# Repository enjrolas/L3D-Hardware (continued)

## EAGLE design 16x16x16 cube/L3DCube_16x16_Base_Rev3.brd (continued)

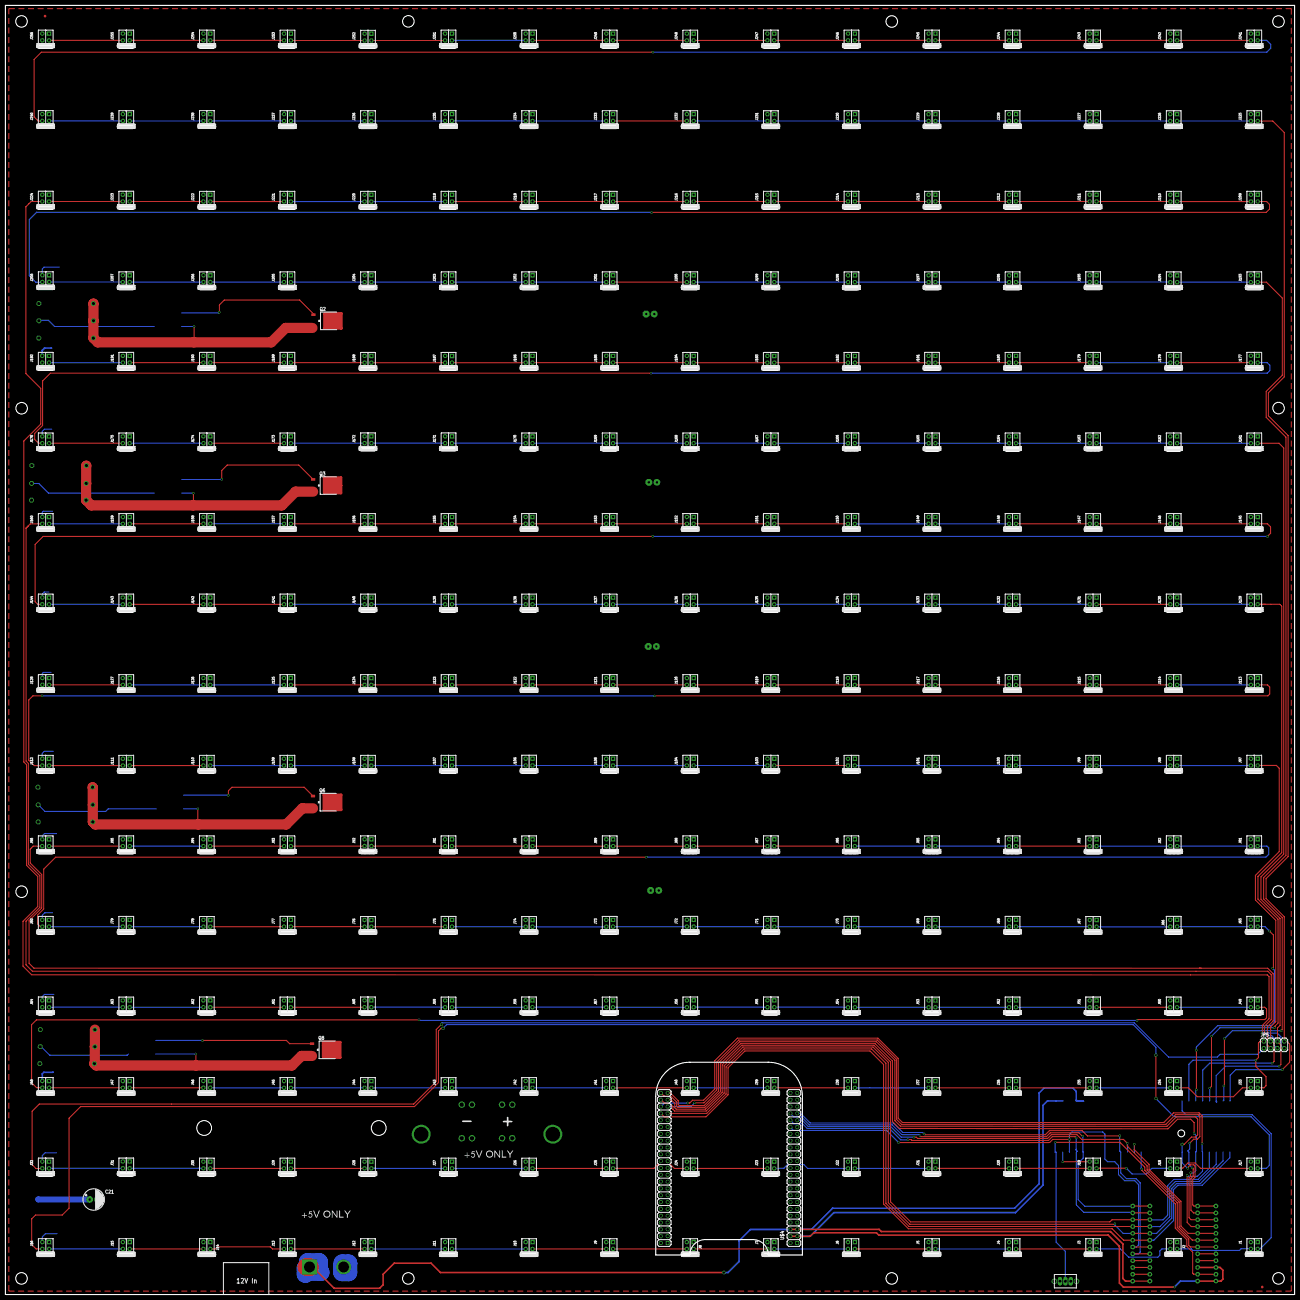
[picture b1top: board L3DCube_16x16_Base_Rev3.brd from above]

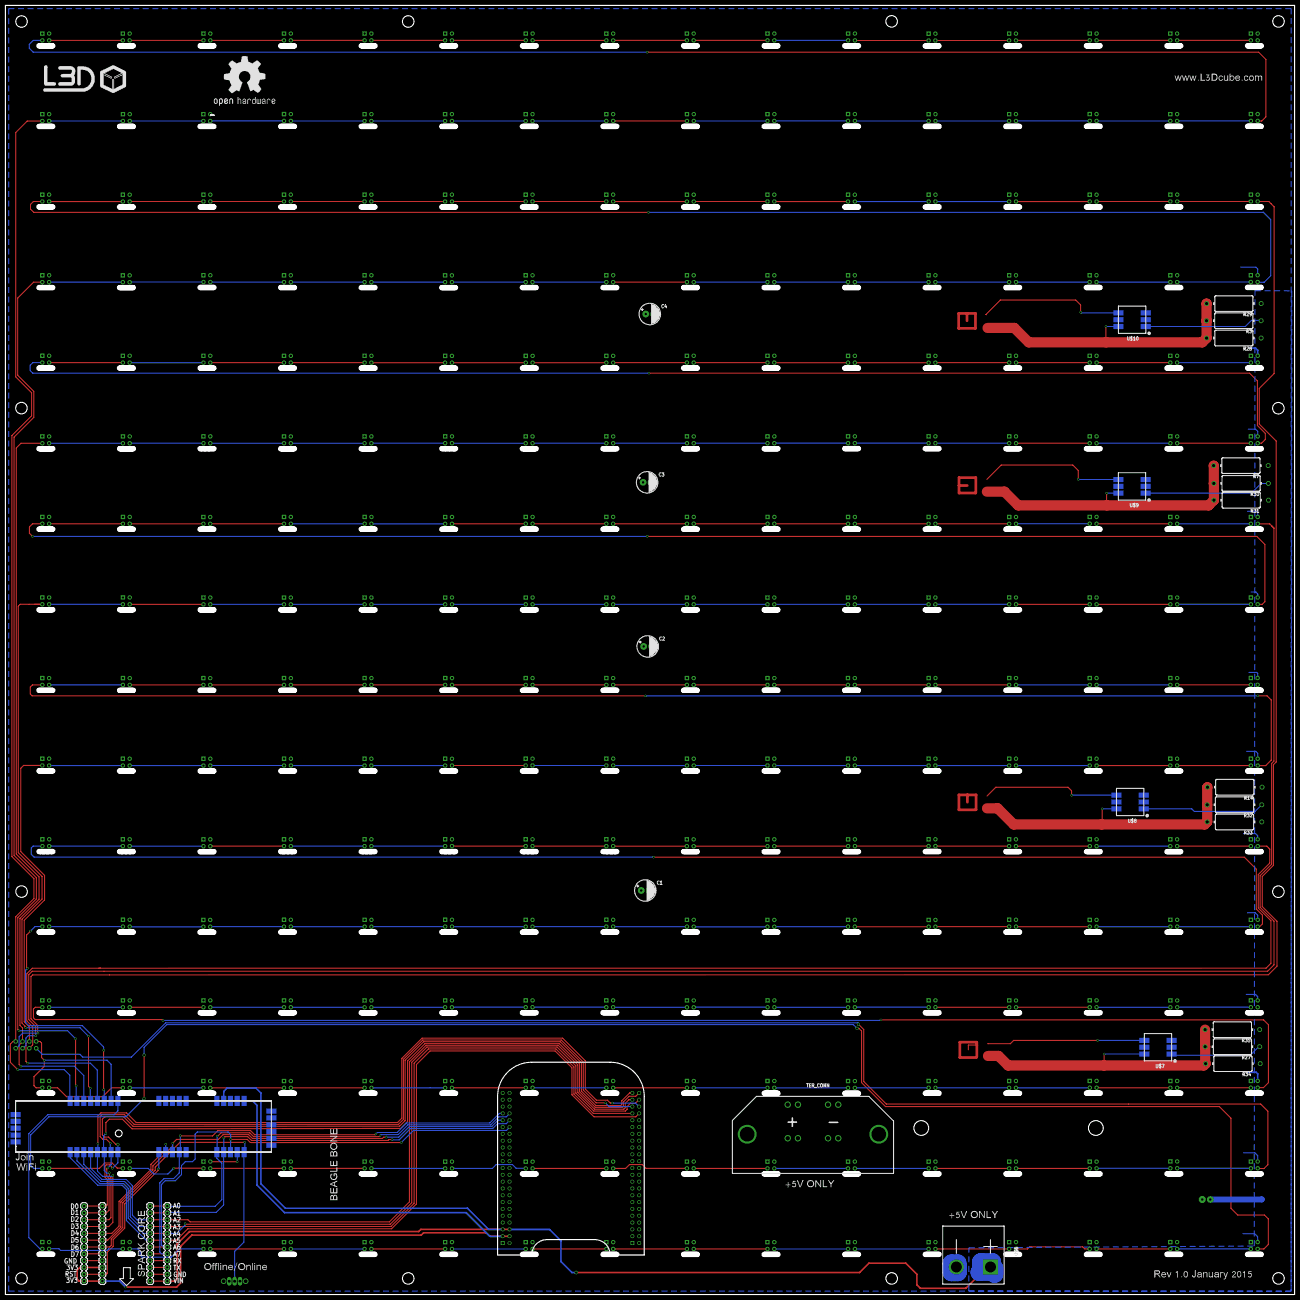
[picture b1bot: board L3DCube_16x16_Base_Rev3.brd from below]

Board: 2 copper layers, 480.0 x 480.0 mm, 295 parts (25 on the bottom side), 291 nets.

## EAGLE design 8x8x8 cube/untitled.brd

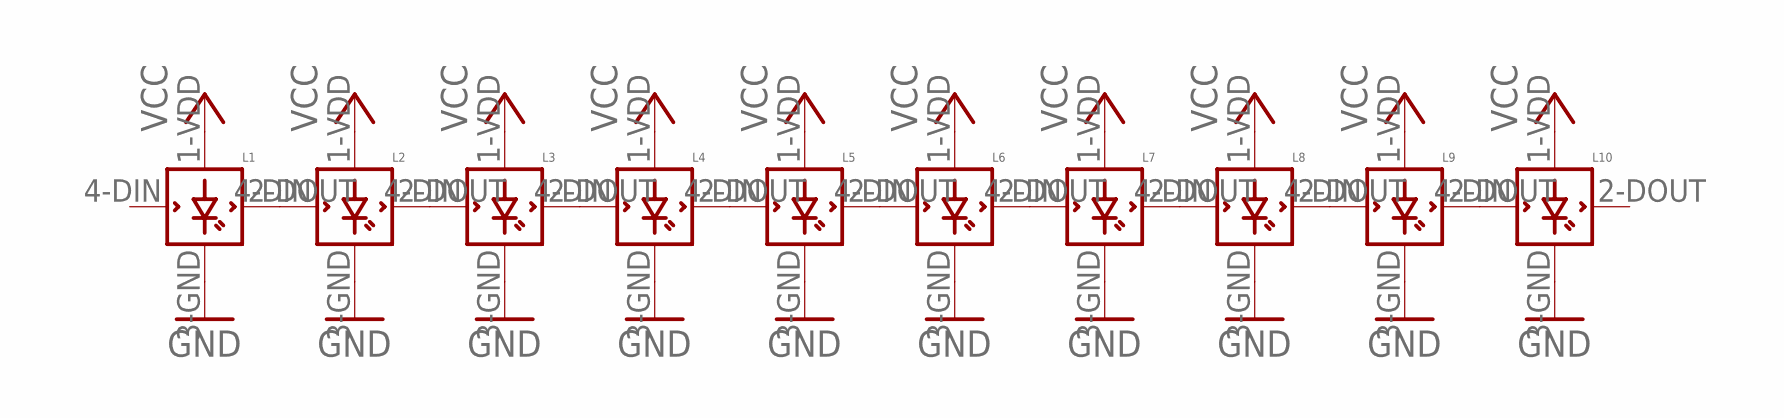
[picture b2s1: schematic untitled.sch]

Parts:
L1, L2, L3, L4, L5, L6, L7, L8, L9, L10: WS2812B

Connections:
GND: L1.3-GND (GND), L2.3-GND (GND), L3.3-GND (GND), L4.3-GND (GND), L5.3-GND (GND), L6.3-GND (GND), L7.3-GND (GND), L8.3-GND (GND), L9.3-GND (GND), L10.3-GND (GND)
unnamed: L1.2-DOUT (DOUT), L2.4-DIN (DIN)
unnamed: L3.2-DOUT (DOUT), L4.4-DIN (DIN)
unnamed: L5.2-DOUT (DOUT), L6.4-DIN (DIN)
unnamed: L7.2-DOUT (DOUT), L8.4-DIN (DIN)
unnamed: L8.2-DOUT (DOUT), L9.4-DIN (DIN)
unnamed: L9.2-DOUT (DOUT), L10.4-DIN (DIN)
VCC: L1.1-VDD (VDD), L2.1-VDD (VDD), L3.1-VDD (VDD), L4.1-VDD (VDD), L5.1-VDD (VDD), L6.1-VDD (VDD), L7.1-VDD (VDD), L8.1-VDD (VDD), L9.1-VDD (VDD), L10.1-VDD (VDD)

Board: 2 copper layers, 10 parts (0 on the bottom side), 8 nets, no tracks yet.

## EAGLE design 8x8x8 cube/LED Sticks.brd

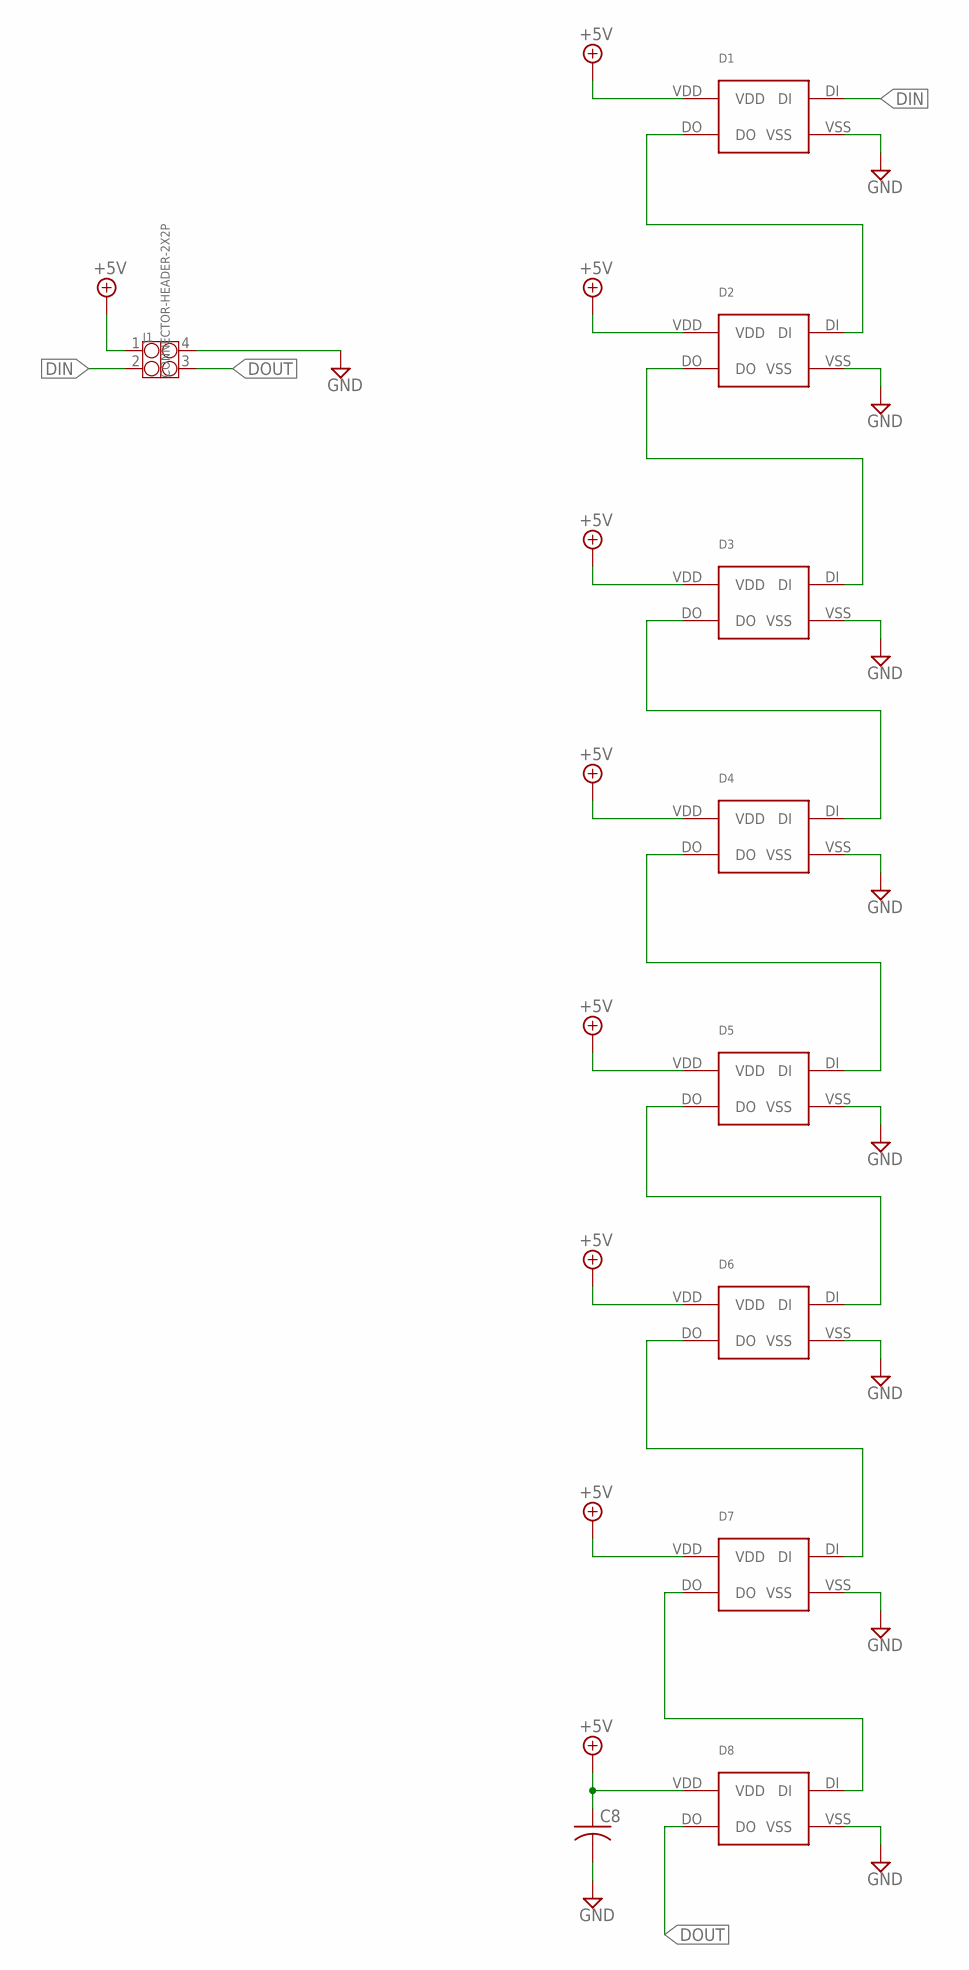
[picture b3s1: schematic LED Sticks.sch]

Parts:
C8: C-USC0603K; C0603K
D1, D2, D3, D4, D5, D6, D7, D8: WS2812B
J1: CONNECTOR-HEADER-2X2P; 2X2P-2.54

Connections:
+5V: C8.1, D1.VDD, D2.VDD, D3.VDD, D4.VDD, D5.VDD, D6.VDD, D7.VDD, D8.VDD, J1.1
DIN: D1.DI, J1.2
DOUT: D8.DO, J1.3
GND: C8.2, D1.VSS, D2.VSS, D3.VSS, D4.VSS, D5.VSS, D6.VSS, D7.VSS, D8.VSS, J1.4
unnamed: D1.DO, D2.DI
unnamed: D2.DO, D3.DI
unnamed: D3.DO, D4.DI
unnamed: D4.DO, D5.DI
unnamed: D5.DO, D6.DI
unnamed: D6.DO, D7.DI
unnamed: D7.DO, D8.DI

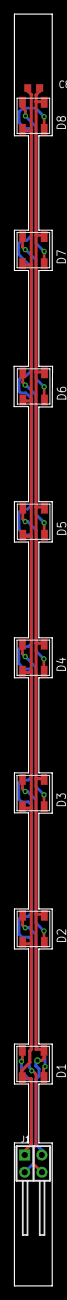
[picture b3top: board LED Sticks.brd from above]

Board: 2 copper layers, 5.7 x 187.5 mm, 10 parts (0 on the bottom side), 11 nets.

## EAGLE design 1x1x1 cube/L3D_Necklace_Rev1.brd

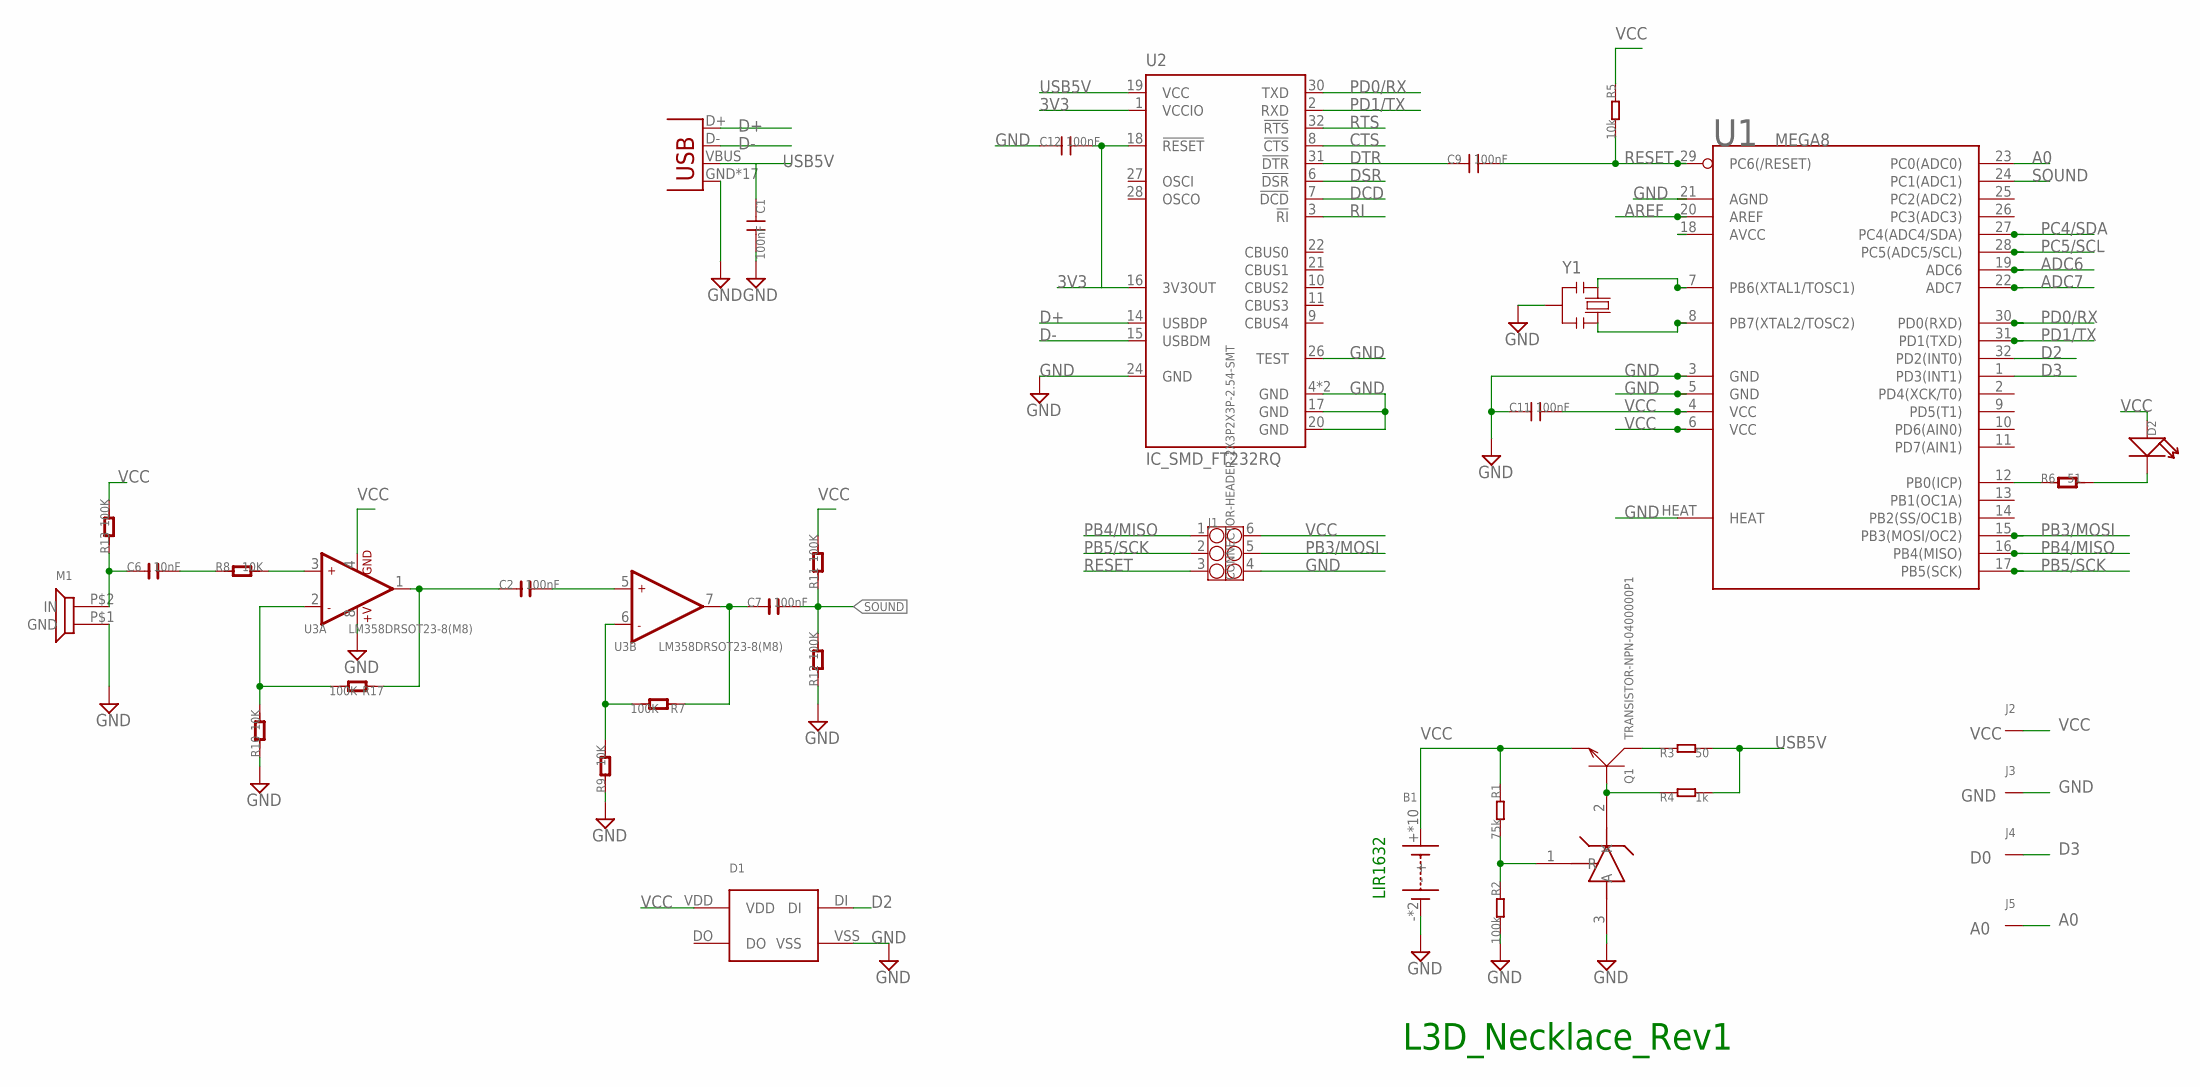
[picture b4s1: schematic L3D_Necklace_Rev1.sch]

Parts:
B1: BUTTONCELLLIR1632; BUTTONCELL_LIR1632
C1, C9, C11, C12: 100nF; 0603
C2, C7: 100nF; C0603
C6: 10nF; C0603
D1: WS2812BWS2812B_STANDARD; WS2812B_STANDARD
D2: LEDLED1206; LED1206
J1: CONNECTOR-HEADER-2X3P2X3P-2.54-SMT; 2X3P-2.54-SMT
J2: VCC; 1R5MM-HOLE
J3: GND; 1R5MM-HOLE
J4: D0; 1R5MM-HOLE
J5: A0; 1R5MM-HOLE
JP1: USBUSB-MICROB-SLOT-HOLE; USB-MICROB-SLOT-HOLE
M1: MICROPHONEMICROPHONE_1*3MM; MICROPHONE_1*3MM
Q1: TRANSISTOR-NPN-0400000P1; SOT23
R1: 75k; 0603
R2: 100k; 0603
R3: 50; 0603
R4: 1k; 0603
R5: 10k; 0603
R6: 51; R0603
R7, R11, R12, R13, R17: 100K; R0603
R8, R9, R10: 10K; R0603
U1: MEGA8; MLF32X
U2: IC_SMD_FT232RQ; IC_SMD_QFN32
U3: LM358DRSOT23-8(M8); SOT-23-8(M8)
Y1: SMARTPRJ_RESONATORMU; SMARTPRJ_RESONATOR
Z1: TL431; SOT23

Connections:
3V3: C12.2, U2.1 (VCCIO), U2.16 (3V3OUT), U2.18 (!RESET)
A0: J5.P$1, U1.23 (PC0(ADC0))
ADC6: U1.19 (ADC6)
ADC7: U1.22 (ADC7)
AREF: U1.20 (AREF)
CTS: U2.8 (!CTS)
D2: D1.DI, U1.32 (PD2(INT0))
D3: J4.P$1, U1.1 (PD3(INT1))
D+: JP1.D+, U2.14 (USBDP)
D-: JP1.D-, U2.15 (USBDM)
DCD: U2.7 (!DCD)
DSR: U2.6 (!DSR)
DTR: C9.1, U2.31 (!DTR)
GND: B1.-, B1.-' (-), C1.2, C11.1, C12.1, D1.VSS, J1.4, J3.P$1, JP1.GND, JP1.MT1 (GND), JP1.MT2 (GND), JP1.MT3 (GND), JP1.MT4 (GND), JP1.MT5 (GND), JP1.MT6 (GND), JP1.MT7 (GND), JP1.MT8 (GND), JP1.MT9 (GND), JP1.MT10 (GND), JP1.MT11 (GND), JP1.MT12 (GND), JP1.P$1 (GND), JP1.P$2 (GND), JP1.P$3 (GND), JP1.P$4 (GND), M1.P$1 (GND), R2.2, R9.1, R10.1, R12.1, U1.3 (GND), U1.5 (GND), U1.21 (AGND), U1.HEAT, U2.4 (GND), U2.17 (GND), U2.20 (GND), U2.24 (GND), U2.26 (TEST), U2.EXP (GND), U3.8 (+V), Y1.2, Z1.3 (A)
unnamed: R1.2, R2.1, Z1.1 (R)
unnamed: Q1.1 (B), R4.1, Z1.2 (K)
unnamed: R8.2, U3.3 (+IN1)
unnamed: Q1.3 (C), R3.1
unnamed: C2.1, R17.1, U3.1 (OUT1)
unnamed: R6.1, U1.12 (PB0(ICP))
unnamed: D2.-, R6.2
unnamed: R10.2, R17.2, U3.2 (-IN1)
unnamed: C7.1, R7.1, U3.7 (OUT2)
unnamed: C2.2, U3.5 (+IN2)
unnamed: R7.2, R9.2, U3.6 (-IN2)
unnamed: C6.2, R8.1
unnamed: C6.1, M1.P$2 (IN), R13.1
PB3/MOSI: J1.5, U1.15 (PB3(MOSI/OC2))
PB4/MISO: J1.1, U1.16 (PB4(MISO))
PB5/SCK: J1.2, U1.17 (PB5(SCK))
PC4/SDA: U1.27 (PC4(ADC4/SDA))
PC5/SCL: U1.28 (PC5(ADC5/SCL))
PD0/RX: U1.30 (PD0(RXD)), U2.30 (TXD)
PD1/TX: U1.31 (PD1(TXD)), U2.2 (RXD)
RESET: C9.2, J1.3, R5.2, U1.29 (PC6(/RESET))
RI: U2.3 (!RI)
RTS: U2.32 (!RTS)
SOUND: C7.2, R11.1, R12.2, U1.24 (PC1(ADC1))
USB5V: C1.1, JP1.VBUS, R3.2, R4.2, U2.19 (VCC)
VCC: B1.+, B1.+1' (+), B1.P$3 (+), B1.P$4 (+), B1.P$5 (+), B1.P$6 (+), B1.P$7 (+), B1.P$8 (+), B1.P$9 (+), B1.P$10 (+), C11.2, D1.VDD, D2.+, J1.6, J2.P$1, Q1.2 (E), R1.1, R5.1, R11.2, R13.2, U1.4 (VCC), U1.6 (VCC), U1.18 (AVCC), U3.4 (GND)
XTAL1: U1.7 (PB6(XTAL1/TOSC1)), Y1.1
XTAL2: U1.8 (PB7(XTAL2/TOSC2)), Y1.3

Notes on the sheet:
L3D_Necklace_Rev1
LIR1632

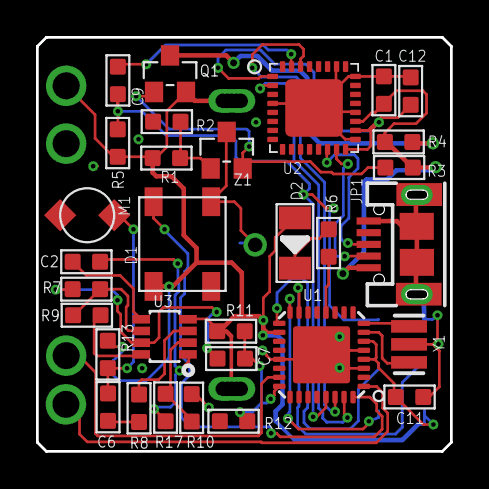
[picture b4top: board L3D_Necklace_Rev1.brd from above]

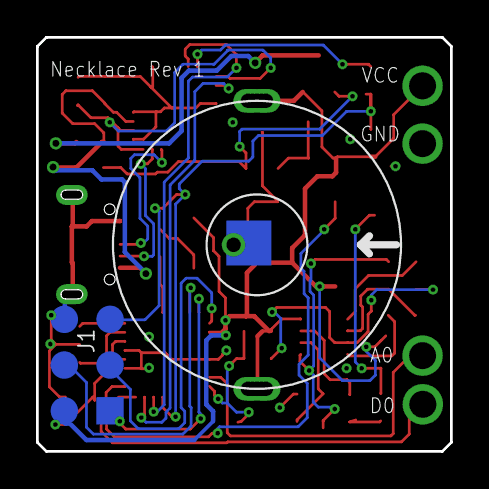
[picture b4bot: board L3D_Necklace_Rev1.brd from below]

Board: 2 copper layers, 23.0 x 23.0 mm, 37 parts (2 on the bottom side), 32 nets.

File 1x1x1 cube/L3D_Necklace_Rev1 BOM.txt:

Partlist exported from /Users/japhy/Downloads/L3D-Hardware-master/1x1x1 cube/L3D_Necklace_Rev1.sch at 4/11/16 1:42 PM

Part Value                              Device                             Package              Description                                                             
B1   BUTTONCELLLIR1632                  BUTTONCELLLIR1632                  BUTTONCELL_LIR1632                                                                           
C1   100nF                              C-0603                             0603                 Ceramic Capacitors                                                      
C2   100nF                              C-0603                             C0603                                                                                        
C6   10nF                               C-0603                             C0603                                                                                        
C7   100nF                              C-0603                             C0603                                                                                        
C9   100nF                              C-0603                             0603                 Ceramic Capacitors                                                      
C11  100nF                              C-0603                             0603                 Ceramic Capacitors                                                      
C12  100nF                              C-0603                             0603                 Ceramic Capacitors                                                      
D1                                      WS2812BWS2812B_STANDARD            WS2812B_STANDARD                                                                             
D2                                      LEDLED1206                         LED1206              LED                                                                     
J1   CONNECTOR-HEADER-2X3P2X3P-2.54-SMT CONNECTOR-HEADER-2X3P2X3P-2.54-SMT 2X3P-2.54-SMT                                                                                
J2   VCC                                1R5MM-HOLE                         1R5MM-HOLE                                                                                   
J3   GND                                1R5MM-HOLE                         1R5MM-HOLE                                                                                   
J4   D0                                 1R5MM-HOLE                         1R5MM-HOLE                                                                                   
J5   A0                                 1R5MM-HOLE                         1R5MM-HOLE                                                                                   
JP1  USBUSB-MICROB-SLOT-HOLE            USBUSB-MICROB-SLOT-HOLE            USB-MICROB-SLOT-HOLE                                                                         
M1   MICROPHONEMICROPHONE_1*3MM         MICROPHONEMICROPHONE_1*3MM         MICROPHONE_1*3MM                                                                             
Q1   TRANSISTOR-NPN-0400000P1           TRANSISTOR-NPN-0400000P1           SOT23                S9013：NPN Transistor                                                    
R1   75k                                R-0603                             0603                                                                                         
R2   100k                               R-0603                             0603                                                                                         
R3   50                                 R-0603                             0603                                                                                         
R4   1k                                 R-0603                             0603                                                                                         
R5   10k                                R-0603                             0603                                                                                         
R6   51                                 R-0603                             R0603                                                                                        
R7   100K                               R-0603                             R0603                                                                                        
R8   10K                                R-0603                             R0603                                                                                        
R9   10K                                R-0603                             R0603                                                                                        
R10  10K                                R-0603                             R0603                                                                                        
R11  100K                               R-0603                             R0603                                                                                        
R12  100K                               R-0603                             R0603                                                                                        
R13  100K                               R-0603                             R0603                                                                                        
R17  100K                               R-0603                             R0603                                                                                        
U1   MEGA8                              MEGA8                              MLF32X                                                                                       
U2   IC_SMD_FT232RQ                     IC_SMD_FT232RQ                     IC_SMD_QFN32         Source: http://www.ftdichip.com/Documents/DataSheets/DS_FT232R_v104.pdf 
U3   LM358DRSOT23-8(M8)                 LM358DRSOT23-8(M8)                 SOT-23-8(M8)         General purpose LOW Voltage, Rail-to-Rail Output Amplifiers             
Y1   SMARTPRJ_RESONATORMU               SMARTPRJ_RESONATORMU               SMARTPRJ_RESONATOR                                                                           
Z1   TL431                              TL431SOT23                         SOT23

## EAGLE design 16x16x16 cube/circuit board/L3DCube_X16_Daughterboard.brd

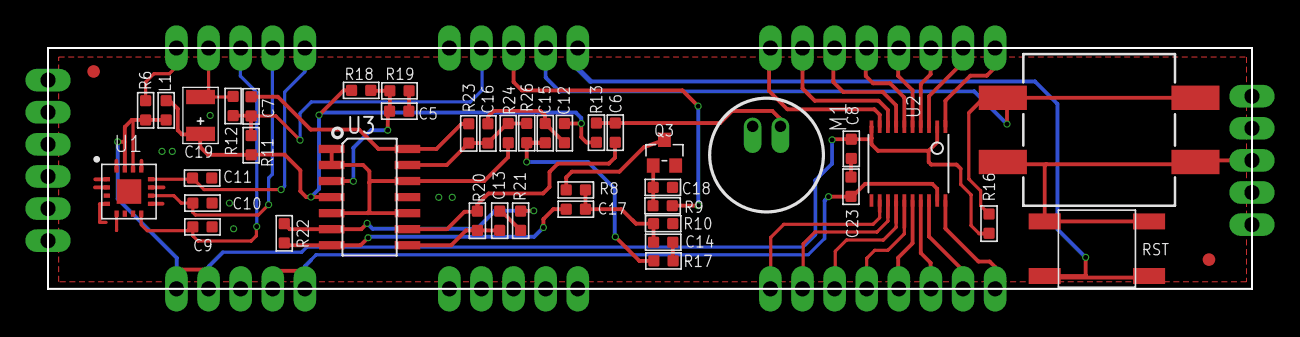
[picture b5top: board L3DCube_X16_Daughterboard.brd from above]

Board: 2 copper layers, 95.2 x 19.1 mm, 44 parts (0 on the bottom side), 43 nets.

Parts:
C5: 10uF; C0603
C6, C7, C8, C9, C10, C11, C12, C13, C18, C23: 100nF; C0603
C14, C17: 220nF; C0603
C15: 10nF; C0603
C16: 680pF; C0603
C19: 220uF; AVX-B
K2: BUTTON-4P; 4P-12X12X6-SMD
L1: 2.2uH; L0603
M1: MICROPHONE
Q3: 2N7002; SOT23
R6, R9, R10, R16, R20, R21, R26: 10K; R0603
R8: 33; R0603
R11, R12, R18, R19: 100K; R0603
R13: 4.3K; R0603
R17: 1K; R0603
R22: 220K; R0603
R23: 180K; R0603
R24: 3.3M; R0603
RST: BUTTON-4P-3100010P1; 4P-SMD-6.0X6.0X5.0H
U1: ADXL335
U2: TSSOP20
U3: LMV324IDR-1100030P1; SOIC14
U$1: CUBE-16-DAUGHTERBOARD
U$2, U$3: FIDUCIAL-MARK

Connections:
!RST: RST.2, RST.3, U$1.RST
+3V3: C8.2, L1.2, R6.1, R16.1, U1.VSS1, U1.VSS2, U2.2, U2.10, U$1.3V3, U$1.3V3'
+5V: C23.2, U2.19, U$1.5V, U$1.5V'
A2: U2.6, U$1.IN3
A3: U2.7, U$1.IN2
A4: U2.8, U$1.IN1
A5: U2.9, U$1.IN0
D0: U2.1, U$1.IN7
D1: U2.3, U$1.IN6
D2: U2.4, U$1.IN5
D3: U2.5, U$1.IN4
DIN_1: U2.20, U$1.OUT7
DIN_2: U2.18, U$1.OUT6
DIN_3: U2.17, U$1.OUT5
DIN_4: U2.16, U$1.OUT4
DIN_5: U2.15, U$1.OUT3
DIN_6: U2.14, U$1.OUT2
DIN_7: U2.13, U$1.OUT1
DIN_8: U2.12, U$1.OUT0
GAIN-CTR: R9.1, U$1.GAIN-CTR
GND: C5.1, C8.1, C9.1, C10.1, C11.1, C12.2, C15.1, C16.1, C18.1, C19.-, C23.1, K2.P$2, K2.P$3, M1.GND, Q3.2, R10.1, R12.1, R19.1, RST.1, RST.4, U1.COM1, U1.COM2, U1.COM3, U1.COM4, U2.11, U3.11, U$1.GND0, U$1.GND1, U$1.GND2, U$1.GND3, U$1.GND4, U$1.GND5, U$1.GND7, U$1.GND8, U$1.GND9, U$1.GND10, U$1.GND11, U$1.GND13, U$1.GND14, U$1.GND15, U$1.GND16, U$1.GND17, U$1.P$37
MIC: C6.1, M1.IN, R13.1
MODE: K2.P$1, K2.P$4, R16.2, U$1.MODE
unnamed: C18.2, Q3.1, R9.2
unnamed: Q3.3, R8.1
unnamed: C14.2, R17.1
unnamed: C15.2, R17.2, R26.1
unnamed: C16.2, R23.1, R24.1, R26.2, U3.13
unnamed: C5.2, R18.1, R19.2, U3.3
unnamed: C6.2, R20.1, U3.9
unnamed: C13.1, R20.2, U3.8
unnamed: C13.2, R21.1
unnamed: R21.2, R22.1, U3.6
unnamed: C14.1, C17.2, R8.2, R10.2
unnamed: C12.1, C19.+, L1.1, R11.2, R13.2, R18.2, U3.4
unnamed: C7.1, R23.2, U3.14
unnamed: C17.1, R22.2, U3.7
REF: R24.2, U3.1, U3.2, U3.5, U3.10, U3.12
SOUND: C7.2, R11.1, R12.2, U$1.SOUND
SWITCH: R6.2, U$1.STEAMING
XOUT: C11.2, U1.X, U$1.XOUT
YOUT: C10.2, U1.Y, U$1.YOUT
ZOUT: C9.2, U1.Z, U$1.ZOUT

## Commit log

2014-09-11 first post
2014-09-25 added LED sticks and acrylic case files
2014-10-01 changed repo name
2014-10-17 added the 16 cube files and separated everything into neat little boxes
2014-10-17 cleaned up removed files
2014-10-17 gitignoring
2014-10-17 gitignorant me
2014-10-17 simple readme
2014-11-15 updated to rev 7
2014-11-25 changed .dxf files to R14 format
2014-12-21 updated lasercut files to christmas cube version (rev 0.7)
2015-02-20 updated files for v2 for the 16x cube
2015-06-03 updated to the kickstarter production cubes
2015-06-03 cleaned up the schematic a bit
2015-06-04 renamed a couple lines in the schematic
2015-11-25 updated 8x bom, schematic and layout for the baseboard
2016-04-11 added BOM for the 1x1x1 cube
2017-03-31 added 16x case files
2017-03-31 added 16x solidworks model for reference
2017-05-29 added firmware to repo
